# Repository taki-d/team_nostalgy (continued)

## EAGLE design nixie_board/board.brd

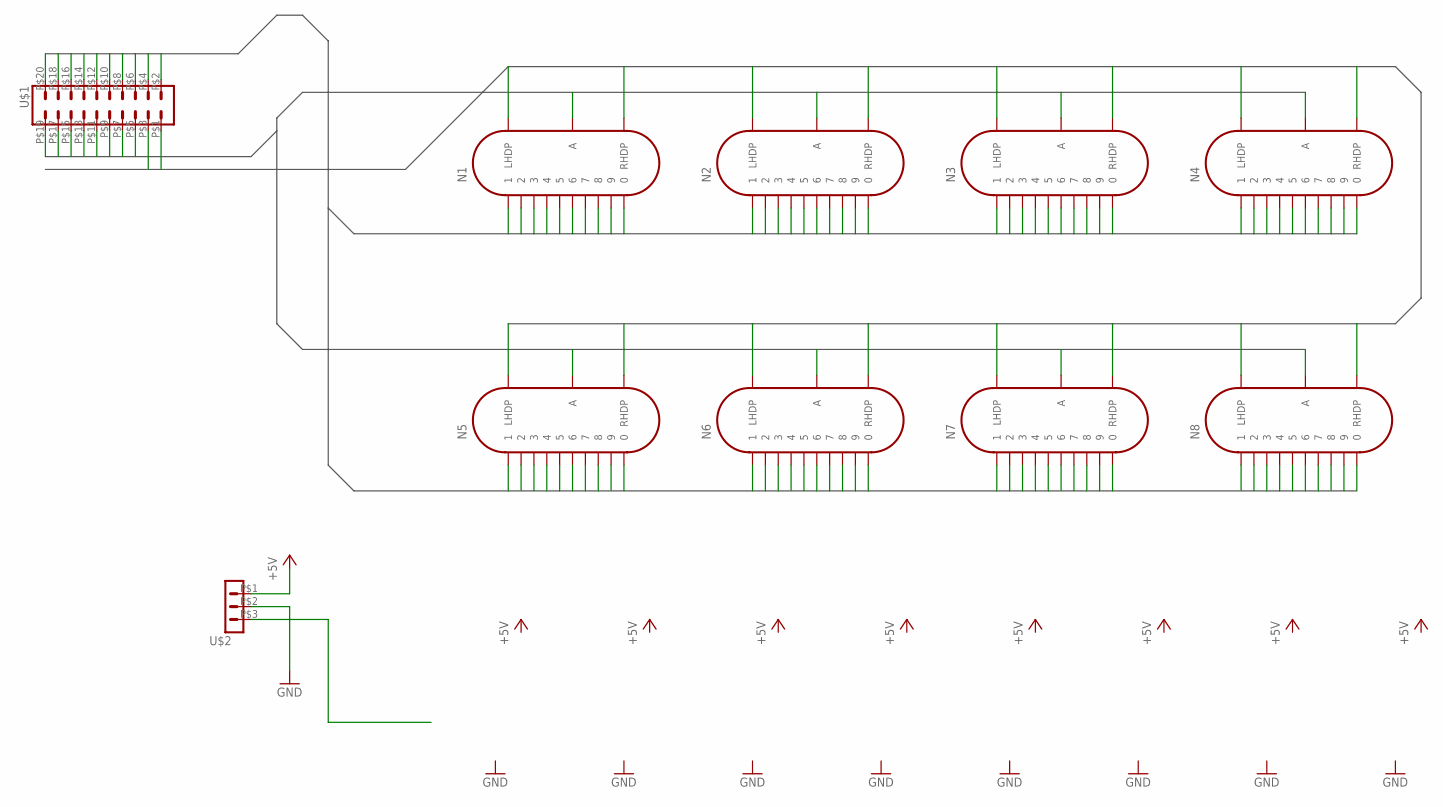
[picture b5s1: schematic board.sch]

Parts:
N1, N2, N3, N4, N5, N6, N7, N8: IN-14
U$1: PIN_HEADER_MALE_2X10_20P
U$2: PIN_HEADER_MALE_1X03_03P

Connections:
+5V: U$2.P$1 (1)
DOT0: N1.LHDP, N2.LHDP, N3.LHDP, N4.LHDP, N5.LHDP, N6.LHDP, N7.LHDP, N8.LHDP, U$1.P$3
DOT1: N1.RHDP, N2.RHDP, N3.RHDP, N4.RHDP, N5.RHDP, N6.RHDP, N7.RHDP, N8.RHDP, U$1.P$1
GND: U$2.P$2 (2)
NIXIE0: N1.0, N2.0, N3.0, N4.0, N5.0, N6.0, N7.0, N8.0, U$1.P$20
NIXIE1: N1.1, N2.1, N3.1, N4.1, N5.1, N6.1, N7.1, N8.1, U$1.P$18
NIXIE2: N1.2, N2.2, N3.2, N4.2, N5.2, N6.2, N7.2, N8.2, U$1.P$16
NIXIE3: N1.3, N2.3, N3.3, N4.3, N5.3, N6.3, N7.3, N8.3, U$1.P$14
NIXIE4: N1.4, N2.4, N3.4, N4.4, N5.4, N6.4, N7.4, N8.4, U$1.P$12
NIXIE5: N1.5, N2.5, N3.5, N4.5, N5.5, N6.5, N7.5, N8.5, U$1.P$10
NIXIE6: N1.6, N2.6, N3.6, N4.6, N5.6, N6.6, N7.6, N8.6, U$1.P$8
NIXIE7: N1.7, N2.7, N3.7, N4.7, N5.7, N6.7, N7.7, N8.7, U$1.P$6
NIXIE8: N1.8, N2.8, N3.8, N4.8, N5.8, N6.8, N7.8, N8.8, U$1.P$4
NIXIE9: N1.9, N2.9, N3.9, N4.9, N5.9, N6.9, N7.9, N8.9, U$1.P$2
NIXIE_ANODE1: N1.A, U$1.P$5
NIXIE_ANODE2: N2.A, U$1.P$7
NIXIE_ANODE3: N3.A, U$1.P$9
NIXIE_ANODE4: N4.A, U$1.P$11
NIXIE_ANODE5: N5.A, U$1.P$13
NIXIE_ANODE6: N6.A, U$1.P$15
NIXIE_ANODE7: N7.A, U$1.P$17
NIXIE_ANODE8: N8.A, U$1.P$19

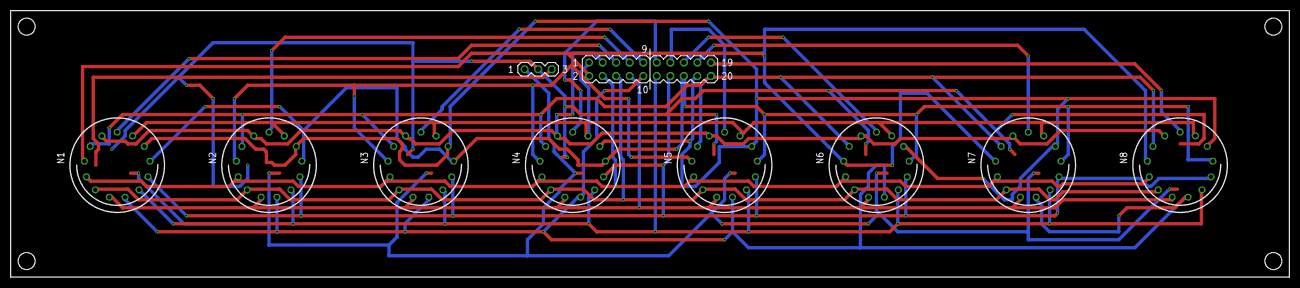
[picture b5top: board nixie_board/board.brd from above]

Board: 2 copper layers, 240.0 x 50.0 mm, 10 parts (0 on the bottom side), 20 nets.

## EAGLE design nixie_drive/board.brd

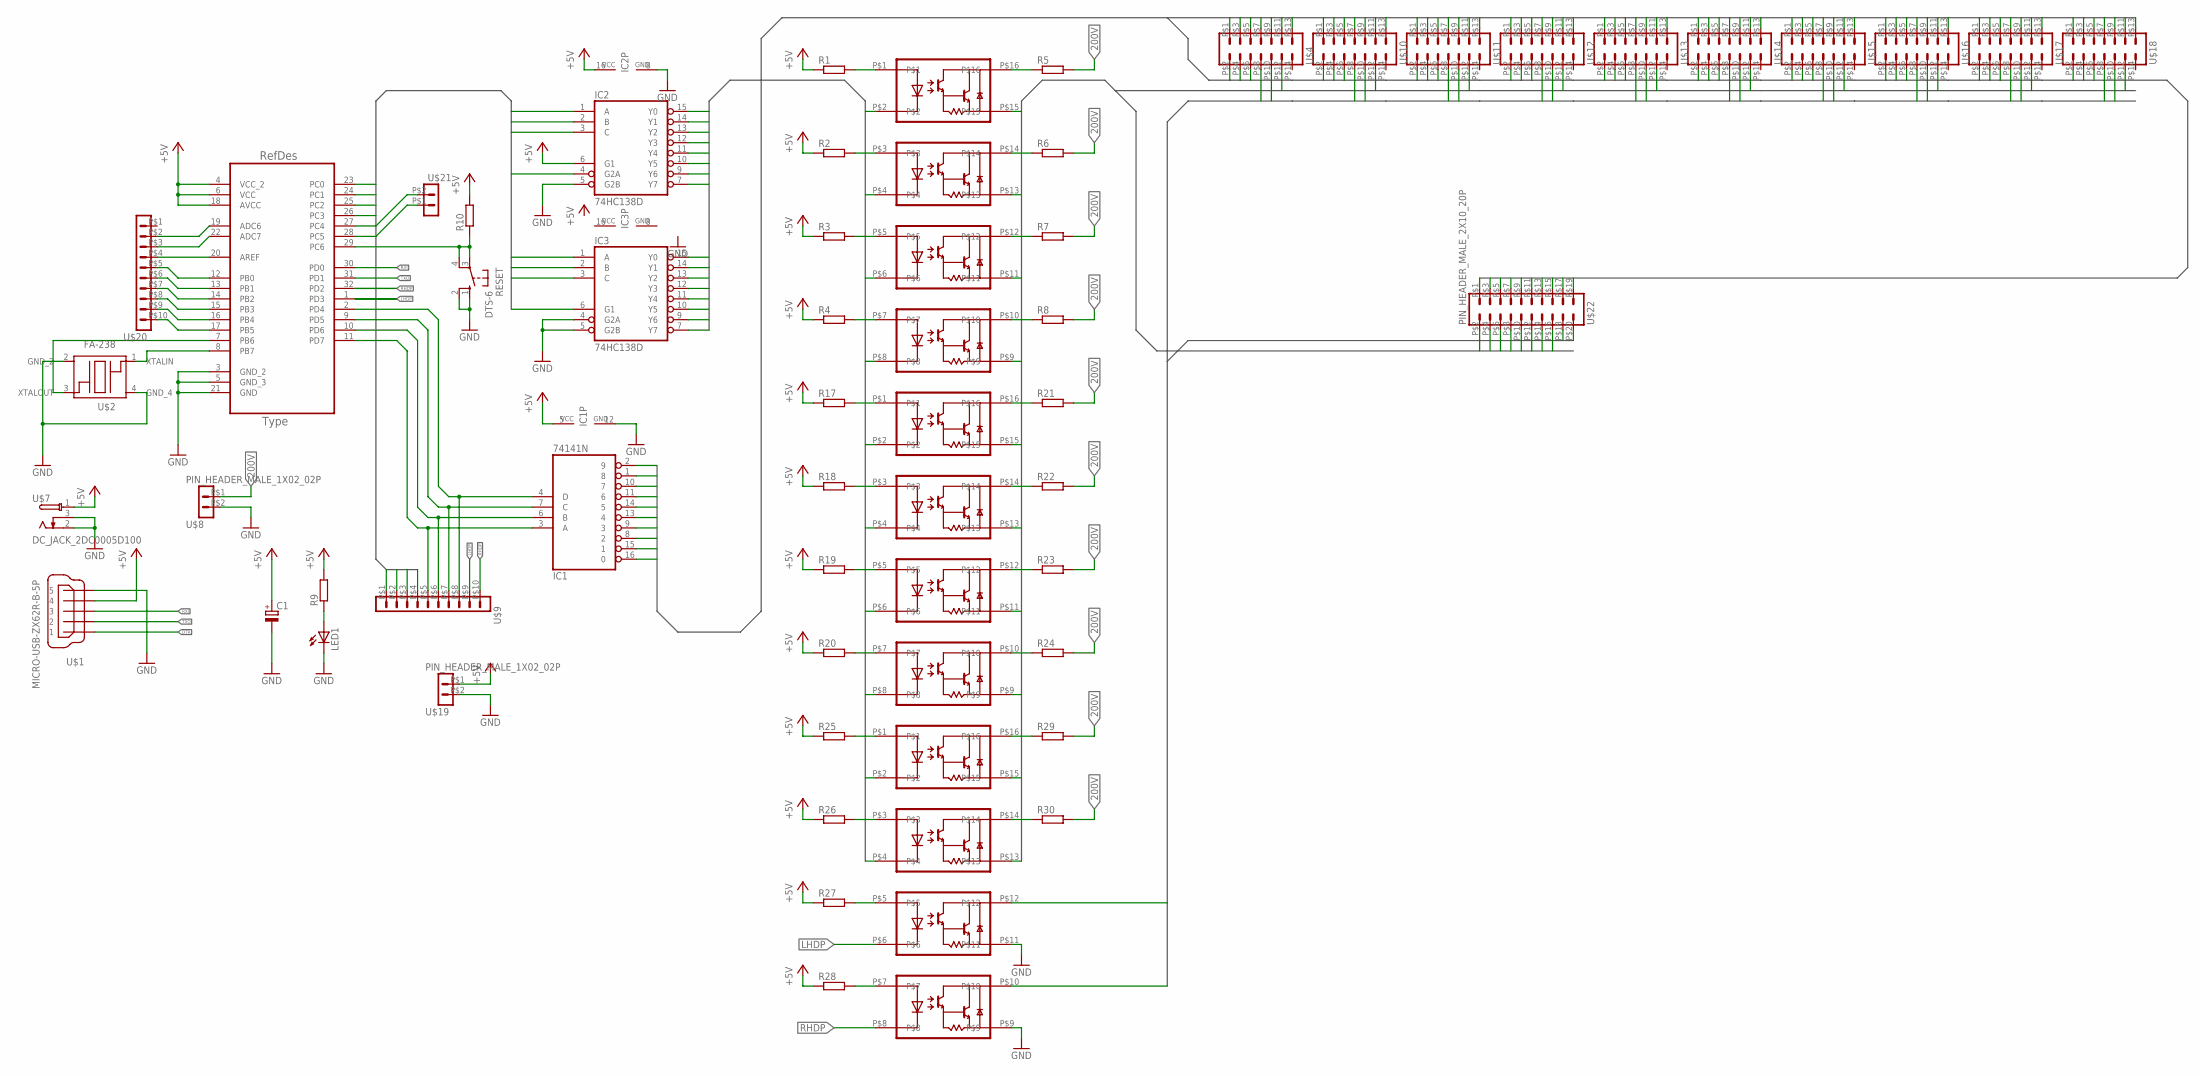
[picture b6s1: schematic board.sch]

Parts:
C1: CPOL-EUE5-8.5; E5-8,5
IC1: 74141N; DIL16
IC2, IC3: 74HC138D; SO16
LED1: LEDSMT1206; 1206
R1, R2, R3, R4, R5, R6, R7, R8, R17, R18, R19, R20, R21, R22, R23, R24, R25, R26, R27, R28, R29, R30: R-EU_M3216; M3216
R9, R10: R-EU_R3216; R3216
RESET: DTS-6; DTS6
U1: ATMEGA328P-AU; QFP80P900X900X120-32N
U$1: MICRO-USB-ZX62R-B-5P; ZX62R-B-5P
U$2: FA-238
U$3, U$5, U$6: TLP627-4
U$4, U$10, U$11, U$12, U$13, U$14, U$15, U$16, U$17, U$18: PIN_HEADER_MALE_2X07_14P
U$7: DC_JACK_2DC0005D100
U$8, U$19, U$21: PIN_HEADER_MALE_1X02_02P
U$9, U$20: PIN_HEADER_MALE_1X10_10P
U$22: PIN_HEADER_MALE_2X10_20P

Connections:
200V: R5.2, R6.2, R7.2, R8.2, R21.2, R22.2, R23.2, R24.2, R29.2, R30.2, U$8.P$1 (1)
+5V: C1.+, IC1.5 (VCC), IC2.6 (G1), IC2.16 (VCC), R1.1, R2.1, R3.1, R4.1, R9.2, R10.2, R17.1, R18.1, R19.1, R20.1, R25.1, R26.1, R27.1, R28.1, U1.4 (VCC_2), U1.6 (VCC), U1.18 (AVCC), U$1.4, U$7.1, U$19.P$1 (1)
ANODE0: IC2.15 (Y0), U$3.P$2
ANODE1: IC2.14 (Y1), U$3.P$4
ANODE2: IC2.13 (Y2), U$3.P$6
ANODE3: IC2.12 (Y3), U$3.P$8
ANODE4: IC2.10 (Y5), U$5.P$2
ANODE5: IC2.11 (Y4), U$5.P$4
ANODE6: IC2.9 (Y6), U$5.P$6
ANODE7: IC2.7 (Y7), U$5.P$8
ANODE8: IC3.15 (Y0), U$6.P$2
ANODE9: IC3.14 (Y1), U$6.P$4
ANODE10: IC3.13 (Y2)
ANODE11: IC3.12 (Y3)
ANODE12: IC3.11 (Y4)
ANODE13: IC3.10 (Y5)
ANODE14: IC3.9 (Y6)
ANODE15: IC3.7 (Y7)
DOT0: U$4.P$8, U$6.P$12, U$10.P$8, U$11.P$8, U$12.P$8, U$13.P$8, U$14.P$8, U$15.P$8, U$16.P$8, U$17.P$8, U$18.P$8, U$22.P$18
DOT1: U$4.P$10, U$6.P$10, U$10.P$10, U$11.P$10, U$12.P$10, U$13.P$10, U$14.P$10, U$15.P$10, U$16.P$10, U$17.P$10, U$18.P$10, U$22.P$20
DTR: U$1.1
GND: C1.-, IC1.12 (GND), IC2.5 (G2B), IC2.8 (GND), IC3.4 (G2A), IC3.5 (G2B), IC3.8 (GND), LED1.C, RESET.1 (S), RESET.2 (S1), U1.3 (GND_2), U1.5 (GND_3), U1.21 (GND), U$1.5, U$2.2 (GND_2), U$2.4 (GND_4), U$6.P$9, U$6.P$11, U$7.2, U$7.3, U$8.P$2 (2), U$19.P$2 (2)
LHDP: U1.1 (PD3), U$6.P$6
unnamed: U1.7 (PB6), U$2.3 (XTALOUT)
unnamed: U1.8 (PB7), U$2.1 (XTALIN)
unnamed: IC1.3 (A), U1.11 (PD7), U$9.P$5 (5)
unnamed: IC1.6 (B), U1.10 (PD6), U$9.P$6 (6)
unnamed: IC1.7 (C), U1.9 (PD5), U$9.P$7 (7)
unnamed: IC1.4 (D), U1.2 (PD4), U$9.P$8 (8)
unnamed: R1.2, U$3.P$1
unnamed: R2.2, U$3.P$3
unnamed: R3.2, U$3.P$5
unnamed: R4.2, U$3.P$7
unnamed: R8.1, U$3.P$10
unnamed: R7.1, U$3.P$12
unnamed: R6.1, U$3.P$14
unnamed: R5.1, U$3.P$16
unnamed: R10.1, RESET.3, RESET.4 (P1), U1.29 (PC6)
unnamed: LED1.A, R9.1
unnamed: U1.17 (PB5), U$20.P$10 (10)
unnamed: U1.16 (PB4), U$20.P$9 (9)
unnamed: U1.15 (PB3), U$20.P$8 (8)
unnamed: U1.14 (PB2), U$20.P$7 (7)
unnamed: U1.13 (PB1), U$20.P$6 (6)
unnamed: U1.12 (PB0), U$20.P$5 (5)
unnamed: R17.2, U$5.P$1
unnamed: R18.2, U$5.P$3
unnamed: R19.2, U$5.P$5
unnamed: R20.2, U$5.P$7
unnamed: R24.1, U$5.P$10
unnamed: R23.1, U$5.P$12
unnamed: R22.1, U$5.P$14
unnamed: R21.1, U$5.P$16
unnamed: R25.2, U$6.P$1
unnamed: R26.2, U$6.P$3
unnamed: R27.2, U$6.P$5
unnamed: R28.2, U$6.P$7
unnamed: U1.20 (AREF), U$20.P$4 (4)
unnamed: U1.22 (ADC7), U$20.P$3 (3)
unnamed: R30.1, U$6.P$14
unnamed: R29.1, U$6.P$16
unnamed: U1.19 (ADC6), U$20.P$2 (2)
unnamed: U1.28 (PC5), U$21.P$1 (1)
unnamed: U1.27 (PC4), U$21.P$2 (2)
NIX1: IC2.1 (A), IC3.1 (A), U1.26 (PC3), U$9.P$1 (1)
NIX2: IC2.2 (B), IC3.2 (B), U1.25 (PC2), U$9.P$2 (2)
NIX3: IC2.3 (C), IC3.3 (C), U1.24 (PC1), U$9.P$3 (3)
NIX4: IC2.4 (G2A), IC3.6 (G1), U1.23 (PC0), U$9.P$4 (4)
NIXIE0: IC1.16 (0), U$4.P$1, U$10.P$1, U$11.P$1, U$12.P$1, U$13.P$1, U$14.P$1, U$15.P$1, U$16.P$1, U$17.P$1, U$18.P$1, U$22.P$1
NIXIE1: IC1.15 (1), U$4.P$3, U$10.P$3, U$11.P$3, U$12.P$3, U$13.P$3, U$14.P$3, U$15.P$3, U$16.P$3, U$17.P$3, U$18.P$3, U$22.P$3
NIXIE2: IC1.8 (2), U$4.P$5, U$10.P$5, U$11.P$5, U$12.P$5, U$13.P$5, U$14.P$5, U$15.P$5, U$16.P$5, U$17.P$5, U$18.P$5, U$22.P$5
NIXIE3: IC1.9 (3), U$4.P$7, U$10.P$7, U$11.P$7, U$12.P$7, U$13.P$7, U$14.P$7, U$15.P$7, U$16.P$7, U$17.P$7, U$18.P$7, U$22.P$7
NIXIE4: IC1.13 (4), U$4.P$9, U$10.P$9, U$11.P$9, U$12.P$9, U$13.P$9, U$14.P$9, U$15.P$9, U$16.P$9, U$17.P$9, U$18.P$9, U$22.P$9
NIXIE5: IC1.14 (5), U$4.P$11, U$10.P$11, U$11.P$11, U$12.P$11, U$13.P$11, U$14.P$11, U$15.P$11, U$16.P$11, U$17.P$11, U$18.P$11, U$22.P$11
NIXIE6: IC1.11 (6), U$4.P$13, U$10.P$13, U$11.P$13, U$12.P$13, U$13.P$13, U$14.P$13, U$15.P$13, U$16.P$13, U$17.P$13, U$18.P$13, U$22.P$13
NIXIE7: IC1.10 (7), U$4.P$2, U$10.P$2, U$11.P$2, U$12.P$2, U$13.P$2, U$14.P$2, U$15.P$2, U$16.P$2, U$17.P$2, U$18.P$2, U$22.P$15
NIXIE8: IC1.1 (8), U$4.P$4, U$10.P$4, U$11.P$4, U$12.P$4, U$13.P$4, U$14.P$4, U$15.P$4, U$16.P$4, U$17.P$4, U$18.P$4, U$22.P$17
NIXIE9: IC1.2 (9), U$4.P$6, U$10.P$6, U$11.P$6, U$12.P$6, U$13.P$6, U$14.P$6, U$15.P$6, U$16.P$6, U$17.P$6, U$18.P$6, U$22.P$19
NIXIE_ANODE1: U$3.P$15, U$4.P$12, U$22.P$16
NIXIE_ANODE2: U$3.P$13, U$10.P$12, U$22.P$14
NIXIE_ANODE3: U$3.P$11, U$11.P$12, U$22.P$12
NIXIE_ANODE4: U$3.P$9, U$12.P$12, U$22.P$10
NIXIE_ANODE5: U$5.P$15, U$13.P$12, U$22.P$8
NIXIE_ANODE6: U$5.P$13, U$14.P$12, U$22.P$6
NIXIE_ANODE7: U$5.P$11, U$15.P$12, U$22.P$4
NIXIE_ANODE8: U$5.P$9, U$16.P$12, U$22.P$2
NIXIE_ANODE9: U$6.P$15, U$17.P$12
NIXIE_ANODE10: U$6.P$13, U$18.P$12
RHDP: U1.32 (PD2), U$6.P$8
RXI: U1.30 (PD0), U$1.3
TXO: U1.31 (PD1), U$1.2
VCC: IC3.16 (VCC)

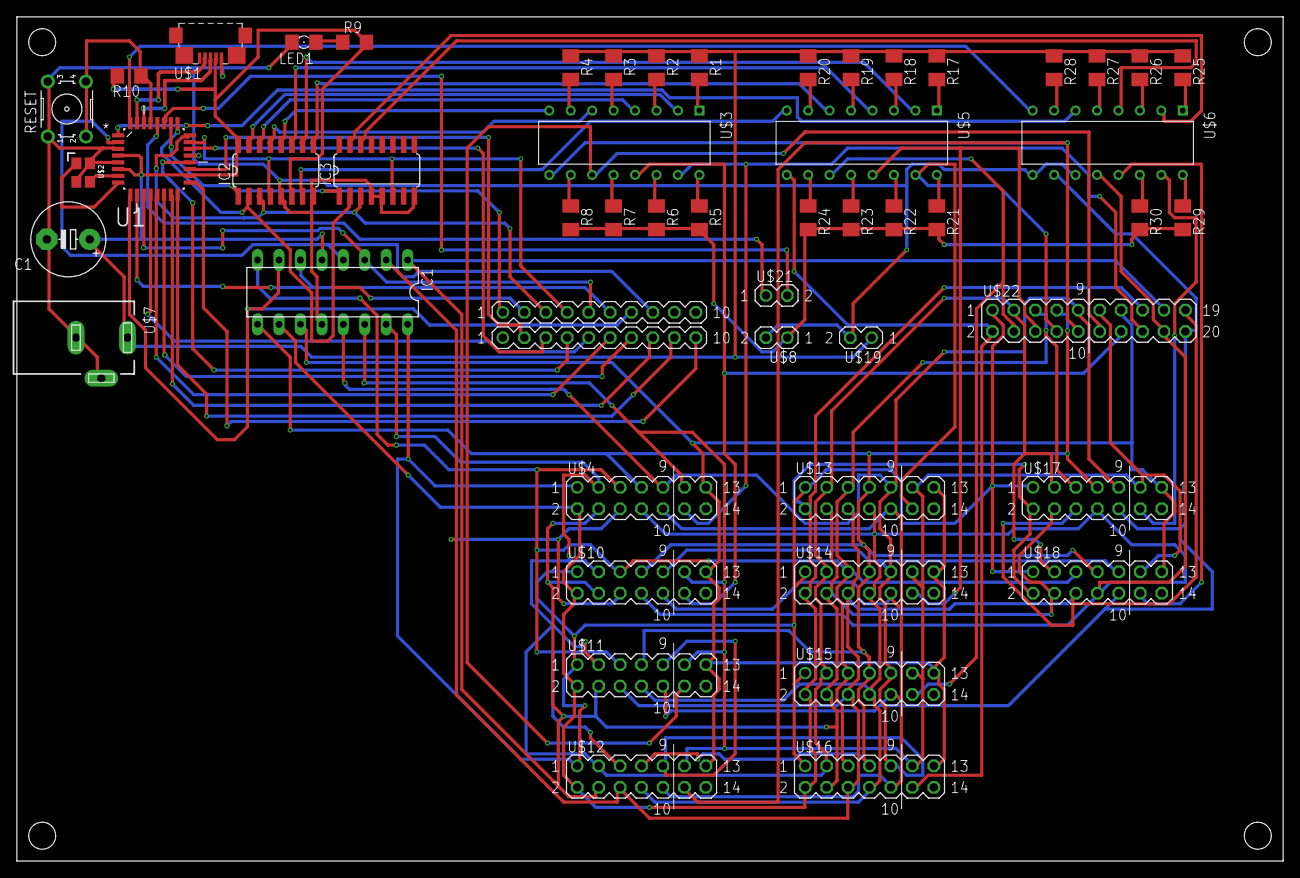
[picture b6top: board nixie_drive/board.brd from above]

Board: 2 copper layers, 150.0 x 100.0 mm, 53 parts (0 on the bottom side), 84 nets.

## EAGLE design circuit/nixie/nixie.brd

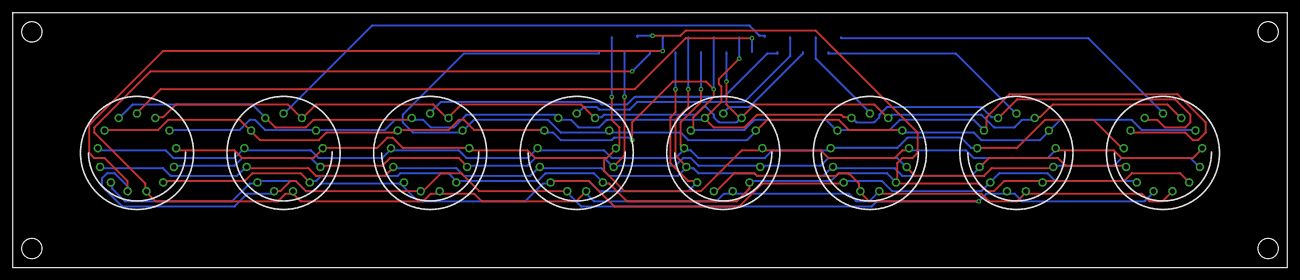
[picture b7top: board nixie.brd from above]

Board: 2 copper layers, 200.0 x 40.0 mm, 9 parts (1 on the bottom side), 20 nets.

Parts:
J4: PSM-210223
N1, N2, N3, N4, N5, N6, N7, N8: IN-14

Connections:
unnamed: J4.1, N1.1, N2.1, N3.1, N4.1, N5.1, N6.1, N7.1, N8.1
unnamed: J4.3, N1.3, N2.3, N3.3, N4.3, N5.3, N6.3, N7.3, N8.3
unnamed: J4.4, N1.4, N2.4, N3.4, N4.4, N5.4, N6.4, N7.4, N8.4
unnamed: J4.5, N1.5, N2.5, N3.5, N4.5, N5.5, N6.5, N7.5, N8.5
unnamed: J4.7, N1.7, N2.7, N3.7, N4.7, N5.7, N6.7, N7.7, N8.7
unnamed: J4.8, N1.8, N2.8, N3.8, N4.8, N5.8, N6.8, N7.8, N8.8
unnamed: J4.9, N1.9, N2.9, N3.9, N4.9, N5.9, N6.9, N7.9, N8.9
unnamed: J4.12, N1.LHDP, N2.LHDP, N3.LHDP, N4.LHDP, N5.LHDP, N6.LHDP, N7.LHDP, N8.LHDP
unnamed: J4.11, N1.RHDP, N2.RHDP, N3.RHDP, N4.RHDP, N5.RHDP, N6.RHDP, N7.RHDP, N8.RHDP
unnamed: J4.2, N1.2, N2.2, N3.2, N4.2, N5.2, N6.2, N7.2, N8.2
unnamed: J4.6, N1.6, N2.6, N3.6, N4.6, N5.6, N6.6, N7.6, N8.6
unnamed: J4.10, N1.0, N2.0, N3.0, N4.0, N5.0, N6.0, N7.0, N8.0
unnamed: J4.13, N1.A
unnamed: J4.14, N2.A
unnamed: J4.15, N3.A
unnamed: J4.16, N4.A
unnamed: J4.17, N5.A
unnamed: J4.18, N6.A
unnamed: J4.19, N7.A
unnamed: J4.20, N8.A

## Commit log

2018-01-17 [add]backup
2018-01-18 [add]iroiro
2018-01-18 [add]add toriaezu
2018-01-18 [add]complete
2018-01-20 [add] 昇降機構のスケッチを追加
2018-01-21 [add] ignoreにstlフォルダを追加
2018-01-21 [fix] いろいろ
2018-01-27 [add] nixie drive circuite add
2018-01-28 [add] add libraly folder and matsu libraly
2018-01-28 [add] add nixie stand
2018-01-28 [add] add switch kikou
2018-01-29 [add] add nixie_switch
2018-01-30 [fix] nixie_switch
2018-01-30 [fix] hole
2018-01-30 [fix] fix hole position
2018-01-30 [add] 横に回転させたやつ
2018-01-30 [add] 面付け
2018-01-31 [add] nixie IN-19A/B
2018-01-31 [fix] name
2018-02-01 [fix] 太さ・ガーバー出力(FusionPCB)
2018-02-02 [fix] nixie_standのsch-brd連携の不具合を解消
2018-02-02 [fix] ガーバーなど
2018-02-20 [update] gitignore
2018-02-20 [fix] switch寸法
2018-02-21 [fix] 足の穴のサイズを変えた
2018-02-24 [add] 回転機構
2018-02-27 [add] ニキシーハンダ
2018-02-28 [add]add arduino sketch
2018-03-01 [fix] はんだ大きさ
2018-03-02 [add]add nixie arduino sketch
2018-03-02 [clean]
2018-03-02 [fix]fix timer interrupt
2018-03-02 [add]add excellent library and command
2018-03-02 [add]add great command
2018-03-02 [add]add dot control command
2018-03-02 [add]create raspberrypi directory and pyhon file
2018-03-02 [add] servo
2018-03-02 [add] 角度とvalの一致
2018-03-02 [add] iroiro
2018-03-04 [add] 組み立てた
2018-03-04 [add]add clock mode
2018-03-04 [fix]fix gitignore
2018-03-04 [fix]fix .gitignore
2018-03-04 [add]add Hello World
2018-03-04 [add]add api
2018-03-04 [fix]fix route
2018-03-04 [add]add template
2018-03-04 [add]add static file
2018-03-04 [add]add index html
2018-03-04 [fix]fix static file location
2018-03-04 [fix]render index.html
2018-03-04 [add]add static file and fix route
2018-03-04 [update]update readme.md
2018-03-04 [add]add nixie display
2018-03-05 [fix] iroiro
2018-03-05 [add] stl
2018-03-05 [add]add page title
2018-03-05 [add]add setledcolor command
2018-03-05 [fix] stlファイルの名前変更
2018-03-06 [fix] 板厚13mmに変更
2018-03-06 [fix] 小さくした
2018-03-06 [update] 小さくした
2018-03-06 [fix] 微調整
2018-03-06 [add]add
2018-03-06 [fix]fix api
2018-03-06 [add]add t/p/h mesure method
2018-03-06 [add] 電圧測定回路を作成
2018-03-07 [fix] huta
2018-03-07 [fix] muki
2018-03-08 [update]update program
2018-03-08 [add] sleepy
2018-09-29 [add]add all
2018-09-30 [add]add adlllllllll
2018-11-19 [clean] clearn directory
2018-11-19 [add]add nixie circuit
2018-11-19 [update]use backup
2018-11-19 [add]add libarar
2018-11-19 [update]separate project
2018-11-19 [fix]fix circuit and board
2018-11-19 [add]add drc
2018-11-20 [add]add all as backup
2018-11-20 [tem@]
2018-11-20 [fix]fix decimal point anode route
2018-11-21 [temp]
2018-11-21 [update]update from thinkpad
2018-11-21 [update]update connector routing
2018-11-21 [add] 時計っぽい何かができた
2018-11-22 [complete]complete vfd driver board
2018-11-23 [add] 起動時にntpによる時刻合わせを実装
2018-11-24 [update] draw outline
2018-11-25 update nixie
2018-11-25 [add]add cam
2018-11-25 [update] update vfd
2018-11-25 [add]add silk
2018-12-18 [add] いろいろ変更
2019-02-21 [update]update firmware
2019-02-21 htmlを作成
2019-02-21 ライブラリをcdnに変更
2019-02-21 ライブラリをcdnに変更 不要な処理を削除
2019-02-21 [add] wi-fi接続ウィザードを作成
2019-02-21 [fix] 接続情報を保存するようにした
2019-02-21 navibarの追加
2019-02-21 ヘルプページ（仮）追加
2019-02-23 [add] nixie_homeを追加
2019-02-23 [add] nixietunes
2019-02-23 [add]add feature of setting func1 func2 from web
2019-02-23 [add]add mode select feature
2019-02-23 [add]add dot api
2019-02-23 [update] dotを追加
2019-02-24 [update]
2019-03-05 [update]update design:wq
2019-06-10 [temp]破壊的変更前の
2019-07-01 [add]add all:wq
2019-07-01 [add]
2019-12-17 [clean
